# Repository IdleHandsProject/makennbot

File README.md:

# Make: Arduino Neural Network Robot
A light avoiding robot that navigates using a Neural Network.

# Watch the Build Series!

BOM Here: https://www.findchips.com/org/10-open-hardware/list/53285-makennbot

HackADay.io Link: https://hackaday.io/project/27938-arduino-neural-network-robot

Motors: https://www.pololu.com/product/2357

OLED: https://www.aliexpress.com/item/White-0-66-inch-OLED-Display-Module-64x48-0-66-LCD-Screen-SPI-for-Arduino-AVR/32782787258.html?spm=a2g0s.9042311.0.0.Wxeht4

Battery(anything with JST SH connector): https://www.sparkfun.com/products/13851

A viewer created a method to train the network using a Python Script, Check it out here: https://github.com/JonComo/Arduino_weight_trainer

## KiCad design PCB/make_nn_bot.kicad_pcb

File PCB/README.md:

# Make: Arduino Neural Network Robot
A light avoiding robot that navigates using a Neural Network.

BOM Here: https://www.findchips.com/org/10-open-hardware/list/53285-makennbot

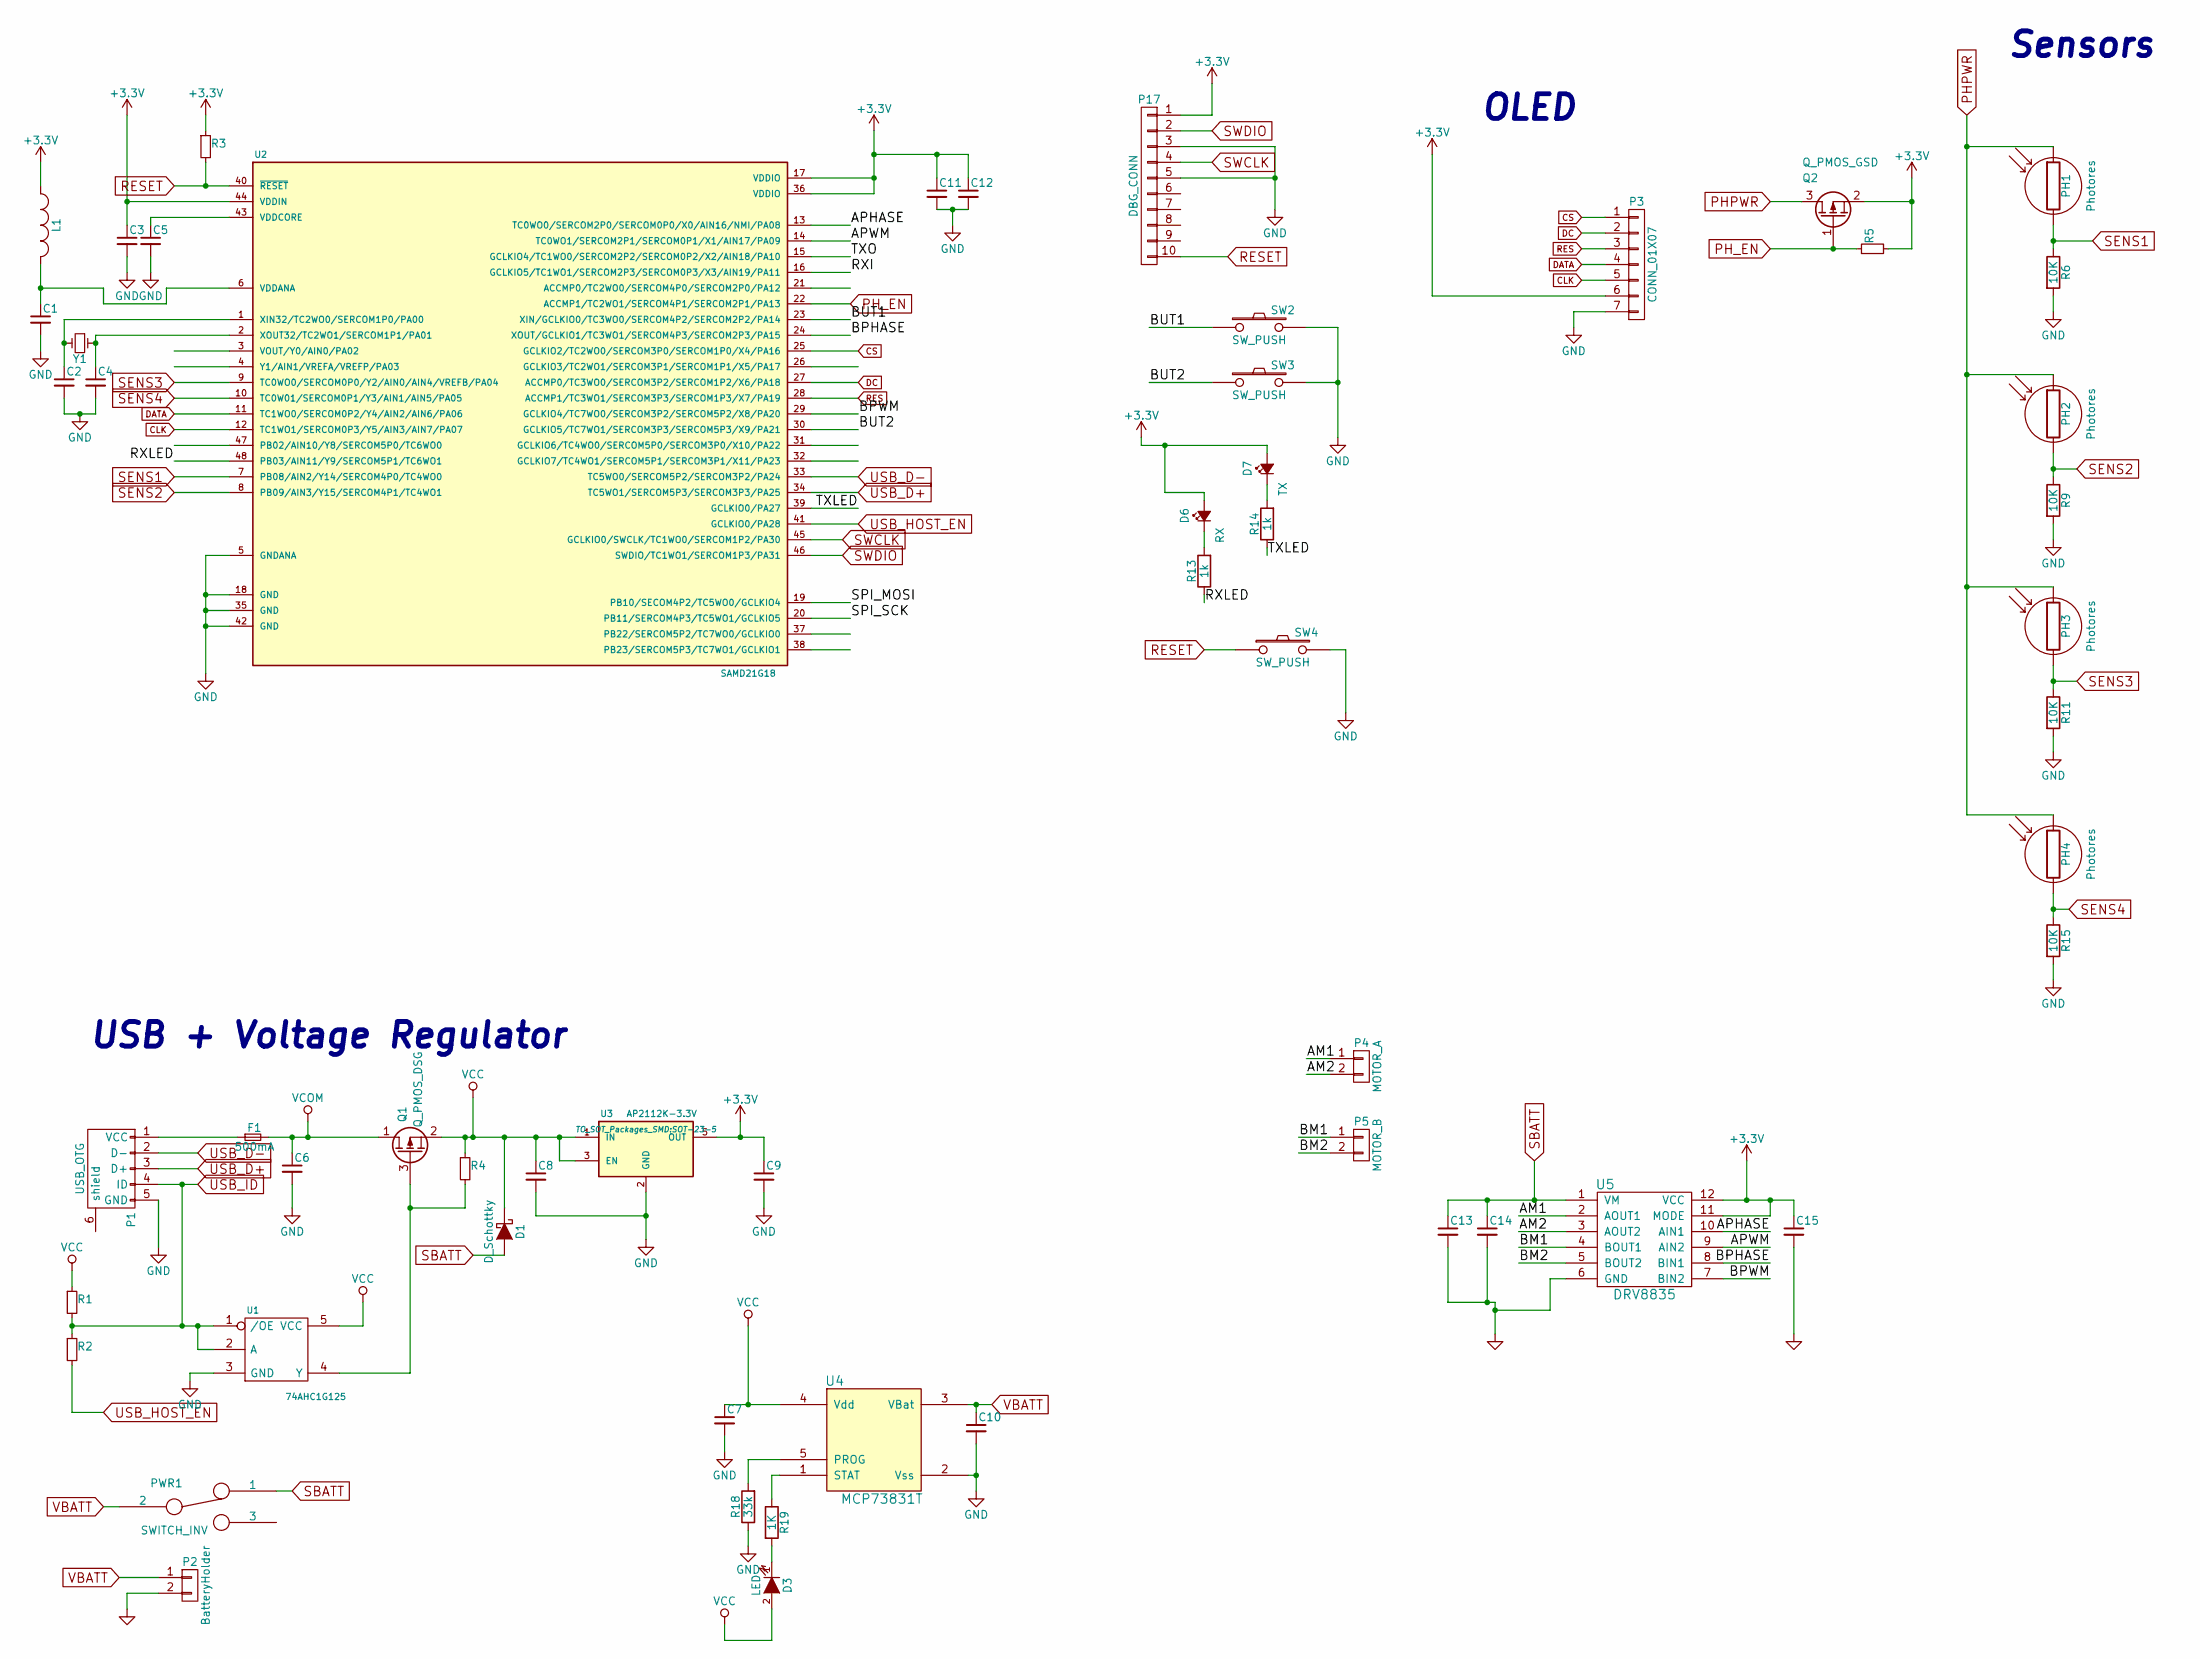
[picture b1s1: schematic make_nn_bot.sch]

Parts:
C1, C3, C5, C11, C12: 0.1uF; C_0603; Digikey Part No. 311-1343-1-ND
C2, C4: 15pF; C_0603; Digikey Part No. 712-1261-1-ND
C6: 2.2uF; C_0603; Digikey Part No. 1276-1291-1-ND
C7, C10: 4.7uF; C_0603; Digikey Part No. 490-5915-1-ND
C8: 1uF; C_0603; Digikey Part No. 490-1320-1-ND
C9: 2.2uF; C_0603; Digikey Part No. 490-10451-1-ND
C13: 10uF; C_0603; Digikey Part No. 311-1729-1-ND
C14, C15: 0.1uF; C_0603; Digikey Part No. 490-6328-1-ND
D1: D_Schottky; sod80c; Digikey Part No. B130-FDICT-ND
D3: LED; LED-0603
D6: RX; Led_0603; Digikey Part No. 160-1447-1-ND
D7: TX; Led_0603; Digikey Part No. 160-1448-1-ND
F1: 500mA; c_1206; Digikey Part No. 507-1803-1-ND
L1: FB - 30Ohm; R_SM0603; Digikey Part No. 445-2986-1-ND
P1: USB_OTG; USB_Micro-B; Digikey Part No. 609-4618-1-ND
P2: BatteryHolder; Connectors_JST_S2B-PH-K; Digikey Part No. 36-2479-ND
P3: CONN_01X07; Pin_Header_Straight_1x07
P4: MOTOR_A; C_1206; Digikey Part No. F3781-ND
P5: MOTOR_B; C_1206; Digikey Part No. F3781-ND
P17: DBG_CONN; Pin_Header_Straight_2x05_Pitch1.27mm; Digikey Part No. 1175-1627-ND
PH1, PH2, PH3, PH4: Photores; Pin_Header_Straight_1x02; Digikey Part No. PDV-P8001-ND
PWR1: SWITCH_INV; Pin_Header_Straight_1x03
Q1: Q_PMOS_DSG; SOT23; Digikey Part No. DMG2307L-7DICT-ND
Q2: Q_PMOS_GSD; SOT23; Digikey Part No. IRLML6402PBFCT-ND
R1: 100k; R_0603; Digikey Part No. 311-100KLRCT-ND
R2: 330; R_0603; Digikey Part No. 311-330JRCT-ND
R3: 10k; R_0603; Digikey Part No. 311-10KJRCT-ND
R4, R5: 47K; R_0603; Digikey Part No. 311-47.0KLRCT-ND
R6, R9, R11, R15: 10K; R_0603; Digikey Part No. 311-10KJRCT-ND
R13, R14: 1k; R_0603; Digikey Part No. 311-1.0KJRCT-ND
R18: 33k; R_0603; Digikey Part No. 311-33KJRCT-ND
R19: 1K; R_0603; Digikey Part No. 311-1.0KJRCT-ND
SW2: SW_PUSH; SW_SPST_EVQPE1; Digikey Part No. CKN9112CT-ND
SW3: SW_PUSH; SW_SPST_EVQPE1; Digikey Part No. CKN9084CT-ND
SW4: SW_PUSH; SW_SPST_EVQPE1; Digikey Part No. 401-1702-1-ND
U1: 74AHC1G125; sot23-5; Digikey Part No. 1727-6024-1-ND
U2: SAMD21G18; TQFP-48_7x7mm_Pitch0.5mm; Digikey Part No. ATSAMD21G18A-AU-ND
U3: AP2112K-3.3V; SOT-23-5; Digikey Part No. AP2112K-3.3TRG1DICT-ND
U4: MCP73831T; sot23-5; Digikey Part No. MCP73831T-2ACI/OTCT-ND
U5: DRV8835; WSON-12-2x3; Digikey Part No. 296-30391-1-ND
Y1: Crystal_Small; crystal_smd_5x3.2mm; Digikey Part No. 631-1002-1-ND

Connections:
+3V3: C3.1, C9.1, C11.1, C12.1, C15.1, D6.2 (A), D7.2 (A), L1.1, P3.6, P17.1, Q2.2 (S), R3.1, R5.2, U2.17 (VDDIO), U2.36 (VDDIO), U2.44 (VDDIN), U3.5 (OUT), U5.11 (MODE), U5.12 (VCC)
/AM1: P4.1, U5.2 (AOUT1)
/AM2: P4.2, U5.3 (AOUT2)
/APHASE: U2.13 (TC0WO0/SERCOM2P0/SERCOM0P0/X0/AIN16/NMI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), U5.10 (AIN1)
/APWM: U2.14 (TC0WO1/SERCOM2P1/SERCOM0P1/X1/AIN17/PA09), U5.9 (AIN2)
/BM1: P5.1, U5.4 (BOUT1)
/BM2: P5.2, U5.5 (BOUT2)
/BPHASE: U2.24 (XOUT/GCLKIO1/TC3WO1/SERCOM4P3/SERCOM2P3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), U5.8 (BIN1)
/BPWM: U2.29 (GCLKIO4/TC7WO0/SERCOM3P2/SERCOM5P2/X8/P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), U5.7 (BIN2)
/BUT1: SW2.1, U2.23 (XIN/GCLKIO0/TC3WO0/SERCOM4P2/SERCOM2P2/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); also elsewhere on the board
/BUT2: SW3.1, U2.30 (GCLKIO5/TC7WO1/SERCOM3P3/SERCOM5P3/X9/P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); also elsewhere on the board
/RXI: U2.16 (GCLKIO5/TC1WO1/SERCOM2P3/SERCOM0P3/X3/A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)
/RXLED: R13.1, U2.48 (PB03/AIN11/Y9/SERCOM5P1/TC6WO1)
/SPI_MOSI: U2.19 (PB10/SECOM4P2/TC5WO0/GCLKIO4)
/SPI_SCK: U2.20 (PB11/SERCOM4P3/TC5WO1/GCLKIO5)
/TXLED: R14.1, U2.39 (GCLKIO0/PA27)
/TXO: U2.15 (GCLKIO4/TC1WO0/SERCOM2P2/SERCOM0P2/X2/A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)
CLK: P3.5, U2.12 (TC1WO1/SERCOM0P3/Y5/AIN3/AIN7/PA07)
CS: P3.1, U2.25 (GCLKIO2/TC2WO0/SERCOM3P0/SERCOM1P0/X4/P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)
DATA: P3.4, U2.11 (TC1WO0/SERCOM0P2/Y4/AIN2/AIN6/PA06)
DC: P3.2, U2.27 (ACCMP0/TC3WO0/SERCOM3P2/SERCOM1P2/X6/PA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)
GND: C1.2, C2.2, C3.2, C4.2, C5.2, C6.2, C7.2, C8.2, C9.2, C10.2, C11.2, C12.2, C13.2, C14.2, C15.2, P1.5 (GND), P2.2, P3.7, P17.3, P17.5, R6.2, R9.2, R11.2, R15.2, R18.1, SW2.2, SW3.2, SW4.2, U1.3 (GND), U2.5 (GNDANA), U2.18 (GND), U2.35 (GND), U2.42 (GND), U3.2 (GND), U4.2 (Vss), U5.6 (GND); also elsewhere on the board
unnamed: C1.1, L1.2, U2.6 (VDDANA)
unnamed: C2.1, U2.1 (XIN32/TC2WO0/SERCOM1P0/PA00), Y1.2
unnamed: C4.1, U2.2 (XOUT32/TC2WO1/SERCOM1P1/PA01), Y1.1
unnamed: C5.1, U2.43 (VDDCORE)
unnamed: D3.1 (K), R19.2
unnamed: D6.1 (K), R13.2
unnamed: D7.1 (K), R14.2
unnamed: F1.1, P1.1 (VCC)
unnamed: Q1.3 (G), R4.2, U1.4 (Y)
unnamed: R18.2, U4.5 (PROG)
unnamed: R19.1, U4.1 (STAT)
PHPWR: PH1.1, PH2.1, PH3.1, PH4.1, Q2.3 (D)
PH_EN: Q2.1 (G), R5.1, U2.22 (ACCMP1/TC2WO1/SERCOM4P1/SERCOM2P1/PA13)
RES: P3.3, U2.28 (ACCMP1/TC3WO1/SERCOM3P3/SERCOM1P3/X7/PA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)
RESET: P17.10, R3.2, SW4.1, U2.40 (~RESET~); also elsewhere on the board
SBATT: C13.1, C14.1, D1.2 (A), PWR1.1, U5.1 (VM)
SENS1: PH1.2, R6.1, U2.7 (PB08/AIN2/Y14/SERCOM4P0/TC4WO0)
SENS2: PH2.2, R9.1, U2.8 (PB09/AIN3/Y15/SERCOM4P1/TC4WO1)
SENS3: PH3.2, R11.1, U2.9 (TC0WO0/SERCOM0P0/Y2/AIN0/AIN4/VREFB/PA04)
SENS4: PH4.2, R15.1, U2.10 (TC0W01/SERCOM0P1/Y3/AIN1/AIN5/PA05)
SWCLK: P17.4, U2.45 (GCLKIO0/SWCLK/TC1WO0/SERCOM1P2/PA30)
SWDIO: P17.2, U2.46 (SWDIO/TC1WO1/SERCOM1P3/PA31)
USB_D+: P1.3 (D+), U2.34 (TC5WO1/SERCOM5P3/SERCOM3P3/PA25)
USB_D-: P1.2 (D-), U2.33 (TC5WO0/SERCOM5P2/SERCOM3P2/PA24)
USB_HOST_EN: R2.2, U2.41 (GCLKIO0/PA28)
USB_ID: P1.4 (ID), R1.2, R2.1, U1.1 (/OE), U1.2 (A)
VBATT: C10.1, P2.1, PWR1.2, U4.3 (VBat)
VCC: C7.1, C8.1, D1.1 (K), D3.2 (A), Q1.2 (S), R1.1, R4.1, U1.5 (VCC), U3.1 (IN), U3.3 (EN), U4.4 (Vdd)
VCOM: C6.1, F1.2, Q1.1 (D)

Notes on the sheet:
USB + Voltage Regulator
Sensors
OLED

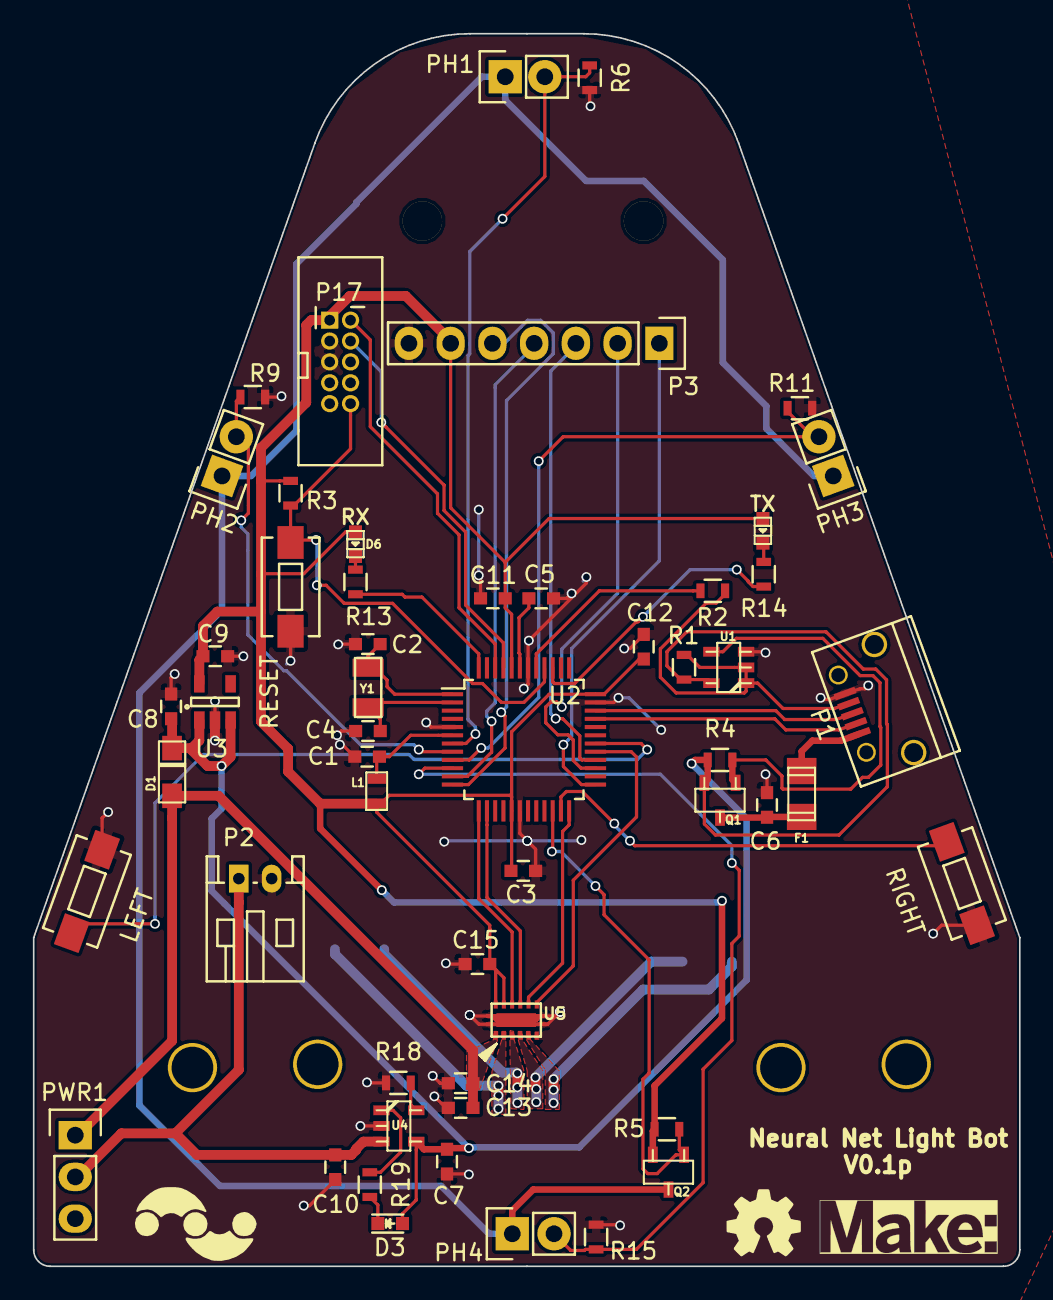
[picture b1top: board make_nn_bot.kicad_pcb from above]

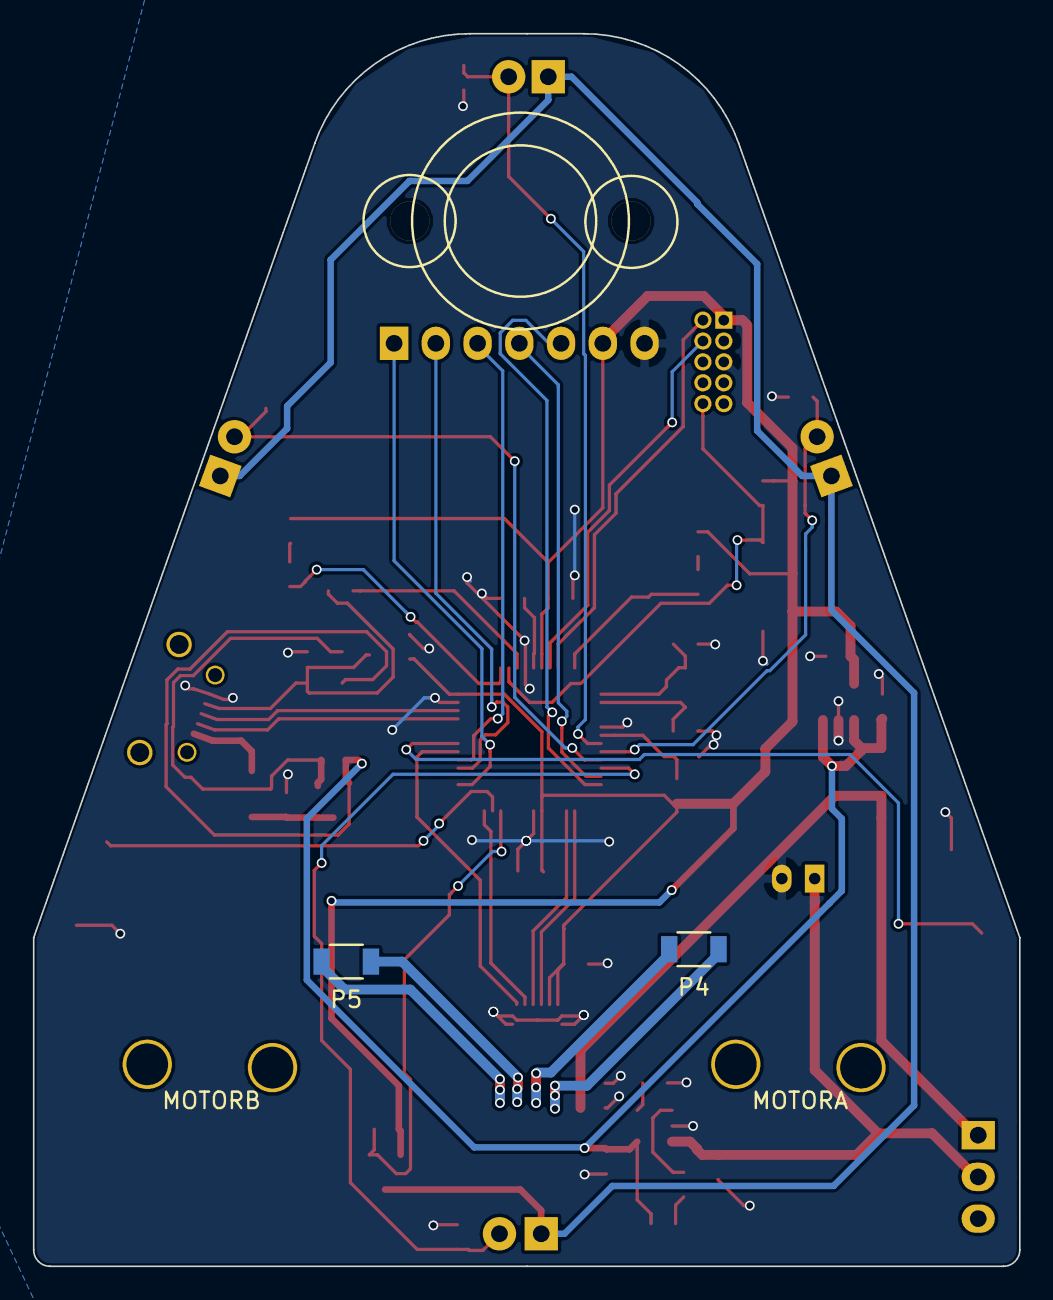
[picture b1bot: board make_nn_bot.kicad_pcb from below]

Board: 2 copper layers, 60.0 x 75.0 mm, 58 parts (4 on the bottom side), 47 nets.

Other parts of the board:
LEFT: SW_PUSH; SW_SPST_EVQPE1
MOTORA: Motor_PlasticGear_Holder
MOTORB: Motor_PlasticGear_Holder
RESET: SW_PUSH; SW_SPST_EVQPE1
RIGHT: SW_PUSH; SW_SPST_EVQPE1

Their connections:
/BUT1: RIGHT.1; also elsewhere on the board
/BUT2: LEFT.1; also elsewhere on the board
GND: LEFT.2, RESET.2, RIGHT.2; also elsewhere on the board
RESET: RESET.1; also elsewhere on the board

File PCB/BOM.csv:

ref,value,footprint,Digikey Part No.,Mouser Part No.,Quantity
C14 C15,0.1uF,Capacitors_SMD:C_0603,490-6328-1-ND,,2
C3 C5 C1 C11 C12,0.1uF,Capacitors_SMD:C_0603,311-1343-1-ND,,5
U4,MCP73831T,idlehands_footprints:sot23-5,MCP73831T-2ACI/OTCT-ND,,1
U5,DRV8835,project_footprints:WSON-12-2x3,296-30391-1-ND,,1
U3,AP2112K-3.3V,TO_SOT_Packages_SMD:SOT-23-5,AP2112K-3.3TRG1DICT-ND,,1
D1,D_Schottky,idlehands_footprints:sod80c,B130-FDICT-ND,,1
R3 R6 R9 R11 R15,10k,Resistors_SMD:R_0603,311-10KJRCT-ND,,5
F1,500mA,project_footprints:c_1206,507-1803-1-ND,,1
C2 C4,15pF,Capacitors_SMD:C_0603,712-1261-1-ND,,2
R18,33k,Resistors_SMD:R_0603,311-33KJRCT-ND,,1
SW2,SW_PUSH,Buttons_Switches_SMD:SW_SPST_EVQPE1,CKN9112CT-ND,,1
Y1,Crystal_Small,project_footprints:crystal_smd_5x3.2mm,631-1002-1-ND,,1
SW3,SW_PUSH,Buttons_Switches_SMD:SW_SPST_EVQPE1,CKN9084CT-ND,,1
D6,RX,project_footprints:Led_0603,160-1447-1-ND,,1
R2,330,Resistors_SMD:R_0603,311-330JRCT-ND,,1
C13,10uF,Capacitors_SMD:C_0603,311-1729-1-ND,,1
U1,74AHC1G125,project_footprints:sot23-5,1727-6024-1-ND,,1
P1,USB_OTG,Connect:USB_Micro-B,609-4618-1-ND,,1
C9,2.2uF,Capacitors_SMD:C_0603,490-10451-1-ND,,1
R1,100k,Resistors_SMD:R_0603,311-100KLRCT-ND,,1
D7,TX,project_footprints:Led_0603,160-1448-1-ND,,1
P17,DBG_CONN,Pin_Headers:Pin_Header_Straight_2x05_Pitch1.27mm,1175-1627-ND,,1
P4 P5,MOTOR_A,Capacitors_SMD:C_1206,F3781-ND,,2
C10 C7,4.7uF,Capacitors_SMD:C_0603,490-5915-1-ND,,2
PH4 PH3 PH2 PH1,Photores,Pin_Headers:Pin_Header_Straight_1x02,PDV-P8001-ND,,4
Q1,Q_PMOS_DSG,project_footprints:SOT23,DMG2307L-7DICT-ND,,1
C6,2.2uF,Capacitors_SMD:C_0603,1276-1291-1-ND,,1
R4 R5,47K,Resistors_SMD:R_0603,311-47.0KLRCT-ND,,2
R14 R13 R19,1k,Resistors_SMD:R_0603,311-1.0KJRCT-ND,,3
Q2,Q_PMOS_GSD,idlehands_footprints:SOT23,IRLML6402PBFCT-ND,,1
U2,SAMD21G18,project_footprints:TQFP-48_7x7mm_Pitch0.5mm,ATSAMD21G18A-AU-ND,,1
C8,1uF,Capacitors_SMD:C_0603,490-1320-1-ND,,1
P2,BatteryHolder,Connectors_JST_PH:Connectors_JST_S2B-PH-K,36-2479-ND,,1
SW4,SW_PUSH,Buttons_Switches_SMD:SW_SPST_EVQPE1,401-1702-1-ND,,1
L1,FB - 30Ohm,project_footprints:R_SM0603,445-2986-1-ND,,1

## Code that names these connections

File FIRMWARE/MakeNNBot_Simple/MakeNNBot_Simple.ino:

#include <Arduino.h>
#include <U8g2lib.h>
#include "make_logo.h"

#ifdef U8X8_HAVE_HW_SPI
#include <SPI.h>
#endif
#ifdef U8X8_HAVE_HW_I2C
#include <Wire.h>
#endif

U8G2_SSD1306_64X48_ER_F_4W_SW_SPI u8g2(U8G2_R0, 9, 8, 11, 10, 12);

int PH1, PH2, PH3, PH4;
int lightSum = 0;
int PHEN = 38;
int menu = 1;
int curr_menu = 1;
int prog_start = 0;
int menu_items = 3;

#define APHASE 4
#define APWM 3
#define BPHASE 5
#define BPWM 6
#define left_b 7
#define right_b 2

void setup() {
  // put your setup code here, to run once:
  pinMode(A1, INPUT);
  pinMode(A2, INPUT);
  pinMode(A3, INPUT);
  pinMode(A4, INPUT);
  pinMode(left_b, INPUT_PULLUP);
  pinMode(right_b, INPUT_PULLUP);

  pinMode(PHEN, OUTPUT);
  digitalWrite(PHEN, LOW);

  SerialUSB.begin(115200);
  delay(100);
  u8g2.begin();

  u8g2.setFlipMode(0);
  u8g2.setFont(u8g2_font_6x12_tr);
  u8g2.setColorIndex(1);

  u8g2.firstPage();
  do {
    drawLogo();
  } while ( u8g2.nextPage() );
  delay(2000);
  u8g2.firstPage();
  do {
    intro();
  } while ( u8g2.nextPage() );
  attachInterrupt(left_b, menu_change, LOW);
  attachInterrupt(right_b, load_prog, LOW);
  delay(1000);
  while (prog_start == 0) {
    u8g2.firstPage();
    do {
      menu_select();
    } while ( u8g2.nextPage() );
  }
  u8g2.clear();
  delay(1000);

}

void loop() {

  //motorTesting() //Run this to test the direction of your motors;

  switch (curr_menu) {
    case 1:
      simpleLightAvoid();
      break;
    case 2:
      
      break;
    case 3:
    
      break;
    default:
      break;

  }
}

void simpleLightAvoid() {
  PH1 = analogRead(A1);
  PH2 = analogRead(A2);
  PH3 = analogRead(A3);
  PH4 = analogRead(A4);
  lightSum = PH1 + PH2 + PH3 + PH4;
  PH1 = map(PH1, 400, 1024, 0, 48);
  PH2 = map(PH2, 400, 1024, 0, 64);
  PH3 = map(PH3, 400, 1024, 0, 64);
  PH4 = map(PH4, 400, 1024, 0, 48);
  //motorTesting();
  u8g2.firstPage();
  do {
    //drawBars(PH1,PH2,PH3,PH4);
    drawBallDir(PH1, PH2, PH3, PH4);
  } while ( u8g2.nextPage() );
}

void drawBallDir(int P1, int P2, int P3, int P4) {
  int pull_x = 0;
  int pull_y = 0;
  pull_x = ((P2 - P3) / 2) + 32;
  pull_y = ((P1 - P4) / 2) + 24;
  u8g2.drawCircle(pull_x, pull_y, 4);
  ballMotorControl(pull_x, pull_y);
}

void ballMotorControl(int mxd, int myd) {
  int  Aspeed = 50;
  int  Bspeed = 50;
  int power = map(myd, 48, 0, 0, 100);
  int offset = map(mxd, 0, 64, 50, -50);
  Aspeed = power - offset;
  Bspeed = power + offset;
  if (Aspeed < 60 && Aspeed > 40) {
    Aspeed = 50;
  }
  if (Bspeed < 60 && Bspeed > 40) {
    Bspeed = 50;
  }
  if (lightSum >3500){
    motorA(65);
    motorB(65);
  }
  else{
  motorA(Aspeed);
  motorB(Bspeed);
  }
}

void motorTesting() {
  SerialUSB.println("Driving Forward");
  motorA(70);
  motorB(70);
  delay(1000);
  SerialUSB.println("Stopping");
  motorA(50);
  motorB(50);
  delay(1000);
  SerialUSB.println("Turning");
  motorA(70);
  motorB(20);

  delay(500);
  motorA(30);
  motorB(30);
  delay(1000);
  motorA(50);
  motorB(50);
  while (1);
}

void drawLogo(void)
{
  uint8_t mdy = 0;
  if ( u8g2.getDisplayHeight() < 59 )
    mdy = 5;
  u8g2.drawBitmap(0, 0, logo_width, logo_height, makelogo_bits);
}

void drawBars(int P1, int P2, int P3, int P4) {
  u8g2.drawBox(1, 1, 10, P1);
  u8g2.drawBox(15, 1, 10, P2);
  u8g2.drawBox(30, 1, 10, P3);
  u8g2.drawBox(45, 1, 10, P4);
  //u8g.print("m/s");

}



void motorA(int percent) {
  int maxSpeed = 90;
  int minSpeed = 10;
  int dir = 0;
  if (percent < 50) {
    dir = 0;
  }
  if (percent > 50) {
    dir = 1;
  }
  if (dir == 1) {
    pinMode(APHASE, INPUT);
    pinMode(APWM, INPUT);
    pinMode(APHASE, OUTPUT);
    pinMode(APWM, OUTPUT);
    digitalWrite(APHASE, LOW);
    int drive = map(percent, 51, 100, 0, 255);
    drive = constrain(drive, 0, 1023);
    //SerialUSB.print("Driving Fore: ");
    //SerialUSB.println(drive);
    analogWrite(APWM, drive);
  }
  if (dir == 0) {
    pinMode(APHASE, INPUT);
    pinMode(APWM, INPUT);
    pinMode(APHASE, OUTPUT);
    pinMode(APWM, OUTPUT);
    digitalWrite(APHASE, HIGH);
    int drive = map(percent, 49, 0, 0, 255);
    drive = constrain(drive, 0, 1023);
    SerialUSB.print("Driving Back: ");
    SerialUSB.println(drive);
    analogWrite(APWM, drive);
  }
  if (percent == 50) {
    pinMode(APHASE, INPUT);
    pinMode(APWM, INPUT);
  }
}

void motorB(int percent) {
  int maxSpeed = 85;
  int minSpeed = 45;
  int dir = 0;
  if (percent < 50) {
    dir = 0;
  }
  if (percent > 50) {
    dir = 1;
  }
  if (dir == 1) {
    pinMode(BPHASE, INPUT);
    pinMode(BPWM, INPUT);
    pinMode(BPHASE, OUTPUT);
    pinMode(BPWM, OUTPUT);
    digitalWrite(BPHASE, HIGH);
    int drive = map(percent, 51, 100, 0, 255);
    drive = constrain(drive, 0, 1023);
    SerialUSB.print("Driving Fore: ");
    SerialUSB.println(drive);
    analogWrite(BPWM, drive);
  }
  if (dir == 0) {
    pinMode(BPHASE, INPUT);
    pinMode(BPWM, INPUT);
    pinMode(BPHASE, OUTPUT);
    pinMode(BPWM, OUTPUT);
    digitalWrite(BPHASE, LOW);
    int drive = map(percent, 49, 0, 0, 255);
    drive = constrain(drive, 0, 1023);
    analogWrite(BPWM, drive);
  }
  if (percent == 50) {
    pinMode(BPHASE, INPUT);
    pinMode(BPWM, INPUT);
  }
}


void intro() {

  u8g2.drawStr( 1, 10, "ANN BOT");
  u8g2.drawStr( 1, 25, "V0.1");
}


void menu_select() {
  menu_circle();
  u8g2.drawStr( 7, 10, "1)Simple");
  u8g2.drawStr( 7, 25, "2)Blank");
  u8g2.drawStr( 7, 40, "3)Blank");
}

void menu_circle() {
  int yloc = curr_menu * 15;
  u8g2.drawCircle(3, yloc - 9, 2);
}

void menu_change(void)
{
  static unsigned long last_interrupt_time = 0;
  unsigned long interrupt_time = millis();
  // If interrupts come faster than 200ms, assume it's a bounce and ignore
  if (interrupt_time - last_interrupt_time > 50)
  {
    int buttState = digitalRead(left_b);
    if (buttState == 0) {
      curr_menu++;
      if (curr_menu > menu_items) {
        curr_menu = 1;
      }
    }
  }
  last_interrupt_time = interrupt_time;
}

void load_prog() {
  prog_start = 1;
}

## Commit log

2017-10-29 added firmware
2017-10-30 Changed README
2017-10-30 README change
2017-10-31 Bootloader added
2017-11-01 Added Title Info
2017-11-06 updated gerbs
2017-11-06 not needed file
2017-11-16 corrected some components
2017-11-17 modified readme
2018-05-12 small revisions
